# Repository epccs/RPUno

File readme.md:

# RPUno 

From <https://github.com/epccs/RPUno/>

## Overview

A general purpose ATmega328p controller board with level shift IO and current sources that operate over the wide input voltage range.

The bare metal microcontroller on this board is the same as an Arduino Uno, I use it to evaluate the examples. Normally C is my preference so converting Arduino's C++ into C adds some overhead, the toolchain supports both but find fewer surprises with C. The toolchain is available on most Linux distributions, a Raspberry Pi makes a nice remote computer and can handle networking services robustly. I use SSH to log in to the remote Raspberry Pi and then I can pull updates from GitHub and run the "Makefile" rules that compile and upload the firmware. The mezzanine board [RPUadpt] or [RPUpi] can be used to add a multidrop serial (rpubus). This controller can turn off its shield VIN pin to power down the Raspberry Pi on RPUpi.

[RPUadpt]: https://github.com/epccs/RPUadpt
[RPUpi]: https://github.com/epccs/RPUpi

[Forum](https://rpubus.org/bb/viewforum.php?f=6)

[HackaDay](https://hackaday.io/project/12784-rpuno)

## Status

Note: bootloader speed has changed from 115.2k to 38.4k bps due to upload errors with the new transceiver on RPUpi^4. Command line serial speed was changed to 38.4k bps some time ago. I have no clue how the bootload upload was working.

[Options](./Hardware#bill-of-materials)

## [Hardware](./Hardware)

Hardware files and notes for referance.

## Example with RPU BUS

This example shows a multidrop serial bus that has several microcontroller boards connected to a single Raspberry Pi computer. Linux on the single board computer controls a hardware UART (/dev/ttyAMA0) that has serial lines connected to a transceiver and its differential pairs. The remote boards have a [RPUadpt] mezzanine board and CAT5 cable daisy-chain between them. 

[Irrigate7]: https://github.com/epccs/Irrigate7

The transceivers are automatically activated, so common serial programs (e.g. avrdude, PySerial, picocom, and UART libraries) work without modification, but care must be taken to ensure only one controller answeres a host command. Each mezzanine board has a bus manager that is used to disconnect all the serial devices when the host connects, only the bootload target controller is connected. The host tells the manager what target to bootload over I2C (either using the local target controller or directly with 328pb second I2C interface). When the target runs its application and reads the bus address over I2C from the manager the manager broadcast a normal mode state that causes all the managers with valid controllers to connect to the serial lines.

I rely on a Command Line Interface (CLI) to the controllers. The CLI responds to commands terminated with a newline (inspired by console), press enter (which sends a newline) to start a command. The command includes an address with the first two bytes, but echo starts after the second byte is sent. The first byte will cause any transmitting device to stop and dump its outgoing buffer which prevents collisions in the data from the controllers to the host. The command length is also limited to allow the use of optimized buffer size.

As a short example, I'll connect with SSH (e.g. from a Windows 1809 build) to a Raspberry Pi Zero board. These machines have matching usernames, with configured SSH keys and known host file from a previous session. Once on the armv61 machine, I use picocom to interact with two different control boards. They are on the same serial bus at addresses '/1' and '/0' (note that ASCII '1' is 0x31, and ASCII '0' is 0x30, so they have an address that looks good on picocom but is probably not what was expected).

```
C:\Users\rsutherland>ssh pi1.local
Linux pi1 4.14.79+ #1159 Sun Nov 4 17:28:08 GMT 2018 armv6l

The programs included with the Debian GNU/Linux system are free software;
the exact distribution terms for each program are described in the
individual files in /usr/share/doc/*/copyright.

Debian GNU/Linux comes with ABSOLUTELY NO WARRANTY, to the extent
permitted by applicable law.
Last login: Sat Feb 16 12:24:59 2019 from 192.168.4.6
rsutherland@pi1:~ $ picocom -b 38400 /dev/ttyAMA0
picocom v1.7

port is        : /dev/ttyAMA0
flowcontrol    : none
baudrate is    : 38400
parity is      : none
databits are   : 8
escape is      : C-a
local echo is  : no
noinit is      : no
noreset is     : no
nolock is      : no
send_cmd is    : sz -vv
receive_cmd is : rz -vv
imap is        :
omap is        :
emap is        : crcrlf,delbs,

Terminal ready
/0/id?
{"id":{"name":"NightLight","desc":"RPUno (14140^9) Board /w atmega328p","avr-gcc":"5.4.0"}}
/1/id?
{"id":{"name":"AmpHr","desc":"RPUlux (17323^2) Board /w atmega328p","avr-gcc":"5.4.0"}}
Ctrl-a,Ctrl-x 
Thanks for using picocom
rsutherland@pi1:~ $ exit
logout
Connection to pi1.local closed.

C:\Users\rsutherland>
```

At present, I'm using [I2Cdebug] to set the manager bootload address. 

[I2Cdebug]: ./i2c-debug

## AVR toolchain

The core files for this board are in the /lib folder. Each example has its files and a Makefile in its own folder. The toolchain packages that I use are available on Ubuntu and Raspbian. 

```
sudo apt-get install make git gcc-avr binutils-avr gdb-avr avr-libc avrdude
git clone https://github.com/epccs/RPUno
```

packages on ubuntu are from Debain

* [gcc-avr](https://packages.ubuntu.com/search?keywords=gcc-avr)
* [binutils-avr](https://packages.ubuntu.com/search?keywords=binutils-avr)
* [gdb-avr](https://packages.ubuntu.com/search?keywords=gdb-avr)
* [avr-libc](https://packages.ubuntu.com/search?keywords=avr-libc)
* [avrdude](https://packages.ubuntu.com/search?keywords=avrdude)

The repository of binutils-avr for Debian is at

https://salsa.debian.org/debian/binutils-avr

The upstream where it was started from is 

https://www.gnu.org/software/binutils/

I don't see any AVR stuff in the upstream. Atmel must have forked it, and Debian is just patching critical material on the fork. Sadly I get the idea that these build tools are the last thing Microchip wants to mess with, I do not blame them it is a cluster, but it could be improved if they would start a public Github or Gitlab repository for these tools so I could have a place to contribute. Ideally, these updates would be added to the upstream, but I suspect that is not practical. Arduino uses these tools also, but they mainly want responsibility for there IDE. 

I place a [Bootloader] on the bare metal microcontroller with a fuse step and a step that uploads using an ISP tool. 

[Bootloader]: https://github.com/epccs/RPUno/tree/master/Bootloader

```
cd RPUno/Bootloader
# note /dev/ttyACM0 is my ICSP tool.
make fuse
make isp
```

The other applications are loaded through the bootloader using the host serial port. Note that the fuse cannot be changed with the bootloader thus reducing user issues with an application upload.

```
cd ~/RPUno/Adc
# note /dev/ttyUSB0 is my FTDI USBuart, and /dev/ttyAMA0 is my Raspberry Pi
make bootload
```

The software is a guide, it is in C because that is my preference for microcontrollers. If you want additional software please add a Github issue to this repository where we can discuss it. 

## Continuous Integration

Continuous Integration (CI) is the practice of automatically compiling and testing each time the mainline source is updated (e.g. git push). Travis CI is using a version of Ubuntu as there host environment for doing the test build. The build machine allows pulling in any packages I want including the AVR cross compiler. I don't do anything fancy, just run make. A rule like "make test" could be used if the test build machine had hardware connected (e.g. "make bootload" and then "make test") to the machine, but that is not practical in the foreseeable future. This was fairly simple to set up for Travis because the ATmega328p was in production at the time the Ubuntu toolchain was done.

[https://travis-ci.org/epccs/RPUno](https://travis-ci.org/epccs/RPUno)

Update: Travis has Ubuntu [Xenial] 16.04.

[Xenial]: https://docs.travis-ci.com/user/reference/xenial/

## Arduino IDE with Arduino 328p Core

The Arduino [IDE] can use the [Uno's AVR core] files that are included (my [core] files are C rather than C++), just remember to look at the schematic to see how the "Uno" is connected.  I do not use the Arduino IDE or C++ (I am a hardware designer,.and have limited intrest in software).

[IDE]: https://www.arduino.cc/
[Uno's AVR core]: https://github.com/arduino/ArduinoCore-avr
[core]: https://github.com/epccs/RPUno/tree/master/lib

## Visual Studio Code

VSC is one of the editors I use, and it is happy with Makefiles. The feature I like most is [IntelliSense], which is configured with JSON files in [.vscode]. 

[IntelliSense]: https://code.visualstudio.com/docs/editor/intellisense
[.vscode]: https://github.com/epccs/RPUno/tree/master/.vscode

The best way to use VSC with GCC (avr-gcc) is in an environment that just works, for me that is Linux, so I can enable [WSL] and install Ubuntu and then use the [Remote WSL].

[WSL]: https://docs.microsoft.com/en-us/windows/wsl/install-win10
[Remote WSL]: https://code.visualstudio.com/docs/remote/wsl

or I can install Linux on a 64bit x86 machine and use [Remote SSH].

[Remote SSH]: https://code.visualstudio.com/docs/remote/ssh

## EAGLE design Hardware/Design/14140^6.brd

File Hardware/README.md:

# Hardware

## Overview

ATmega328p based controller board with options for DIN mounts and 3.5mm spaced through-hole for user connections and headers. Eight level shifted (same as VIN range) digital I/O (10, 11, 12, 13, 14*, 15*, 16*, 17*), the last four (*) are analog channels (0, 1, 2, 3). Four 22mA current source used with loop sensors are available with enables (5, 6, 3, 4). One 17mA current source for a pulse sensor and it has an enable (7). ICP1 is pulled down when enough current (>7mA) arrives from the pulse sensor. Alternate power input may be enabled (9), and power to the shield VIN pin may be disabled (2). Power with 7 thru 36V DC.

The ATmega328p can be programmed with the GCC based toolchain for AVR found in Debian packages (it is available on, Ubuntu, Raspbian, Mac via brew, Windows via Windows Subsystem for Linux). Bootloader options include [optiboot] and [xboot]. Serial bootloaders cannot change the hardware fuse setting which reduces the occurrence of accidentally bricking the controller (I recommend using a serial bootloader during application development). Note that [optiboot] clears the watchdog so it will not get stuck in a watchdog loop.

[optiboot]: https://github.com/Optiboot/optiboot
[xboot]: https://github.com/alexforencich/xboot

## Inputs/Outputs/Functions

```
        Toolchain: gcc-avr binutils-avr gdb-avr avr-libc avrdude
        Wide input power range from 7..36V DC
        High side current sense on input power connected to ADC6.
        Input power voltage is divided down and connected to ADC7.
        Eight digital input/outputs (10,11,12,13,14*,15*,16*,17*) with level conversion.
        Four of the DIO may be used for ADC (*) channels 0..3 (ADC0,ADC1,ADC2,ADC3)
        Four 22mA current sources with enable (3,4,5,6).
        One 17mA current source with enable (7).
        Power to the shield VIN pin may be disabled (2).
        Alternate power input may be enabled (9).
        MCU power (+5V) is converted with an SMPS from the 7..36V input power.
```

## Uses

```
        General Purpose Control for Automation
            Bare Matal (e.g. infinite main loop checks inputs, performs algorithm, and writes outputs)
        Data Acquisition using Capture Hardware (ICP1).
            Flow Meter
            Rotating Hardware
            Pulse Output Temperature Sensors
            Pulse Output Capacitance Sensors
        Automation
            Shield VIN pin can power down a Raspberry Pi on the RPUpi shield.
            A current source may string through inputs of multiple Solid State Relays to control multi-phase power.
            Program in C with an open source toolchain (e.g. GCC, avrdude...).
```

## Notice

```
        ADC4 and ADC5 are used for I2C exclusively and not routed to the analog header.
        AREF from ATmega328p is not routed to the header.
        3V3 is not present on the board, the header pin is not connected.
```

# Table Of Contents

1. [Status](#status)
2. [Design](#design)
3. [Bill of Materials](#bill-of-materials)
4. [Assembly](#assembly)
5. [How To Use](#how-to-use)

# Status

```
        ^9  Done: Design, Layout, BOM, Review*, Order Boards, Assembly, Testing,
            WIP: Evaluation.
            Todo: 
            *during review the Design may change without changing the revision.
            Remove ICP1 10mA pull-up
            Replace digital curr sources with CS2 and CS3
            Replace IO3 and IO4 with ADC2 and ADC3
            Swap MOSI (IO11) with ADC3
            Use IO3 and IO4 to enalbe 22mA CS2 and CS3
            Add level shift to ADC0 and ADC1 so they can be used as digital IO
            Add bootload port (e.g. for Adafruit Friend)
            Add alternate power input (e.g. disconnect a solar pannel to stop charge)
            Pull-down IO9 and 100k ohm on zener to make sure alt power is off at init

        ^8  Done: Design, Layout, BOM, Review*, Order Boards,
            all boards scraped, no assembly done

        ^7  Done: Design, Layout, BOM, Review*, Order Boards, Assembly, Testing,
            WIP: Evaluation.
            use an ESD_NODE like Irrigate7.
            don't turn off the current source used with digital outputs since the digital IO's can do that. 
            DIO protection resistor (change 182 Ohm to 127 Ohm)
            remove LT3652 and reduce size of board.
            add an IDC connector for everything that was used with LT3652 (5,6,7,ADC2,ADC3).
            add JSK plug for I2C
            location: 2017-11-1 reflow oven.

        ^6  two test units (T1,T2) made, four units made to see if anyone is intrested.
            location: 2017-3-24 T1^6 damaged MCU while taking power example image.
                    2017-3-25 T2^6 using on test bench.
                    2017-6-12 T1^6 replaced MCU from a scrped RPUno^4 and tested again.
                    2017-7-19 T2^6 + RPUadpt^5 in SEncl NightLight testing.
                    2017-8-26 T2^6 NightLight ended, unit is in an enclosure with battey but is not in use.
                    2018-4-15 T1 and T2 scap.

        ^5  only unit of this version made
            location: 2016-12-18 Test Bench /w an RPUpi^1, start power management testing
                    2017-1-1 had ADC7 parts (and BOM) changed to measre battery.
                    2017-1-5 had ADC6 hacked to measure raw PV.
                    2017-2-4 moved to SWall Encl /w K3^1, RPUadpt^4, SLP003-12U, 12V battery.
                    2017-3-19 remove 10k thermistor which was used by  LT3652 to turn off chrg when over 40 C
                    2017-4-17 running Solenoid fw, @ SWall Encl, Update K3^2, Update RPUadpt^5, SLP003-12U, 12V battery.
```

Debugging and fixing problems i.e. [Schooling](./Schooling/)

Setup and methods used for [Evaluation](./Evaluation/)

# Design

The board is 0.063 thick, FR4, two layer, 1 oz copper with ENIG (gold) finish.

## Electrical Parameters

```
Power Voltage: 7 thru 36V
```

## Mounting

```
        DIN rail
```

## Electrical Schematic

## Testing

Check correct assembly and function with [Testing](./Testing/)

# Bill of Materials

The BOM is a CVS file, import it into a spreadsheet program like LibreOffice Calc (or Excel), or use a text editor.

Option | BOM's included
----- | ----- 
A. | [BRD] 
M. | [BRD] [SMD] [HDR] 
W. | [BRD] [SMD] [HDR] [PLUG]
Z. | [BRD] [SMD] [HDR] [PLUG] [DIN]

[BRD]: ./Design/14140BRD,BOM.csv
[SMD]: ./Design/14140SMD,BOM.csv
[HDR]: ./Design/14140HDR,BOM.csv
[PLUG]: ./Design/14140PLUG,BOM.csv
[DIN]: ./Design/14140DIN,BOM.csv

[Order Form](https://rpubus.org/Order_Form.html)

# Assembly

## SMD

The board is assembled with CHIPQUIK no-clean solder SMD291AX (RoHS non-compliant). 

The SMD reflow is done in a Black & Decker Model NO. TO1303SB which has the heating elements controlled by a Solid State Relay and an ATMega328p loaded with this [Reflow] firmware.

[Reflow]: https://github.com/epccs/RPUno/tree/master/Reflow

# How To Use

The application should have a wiring diagram to show the setup.

## Solar

Trickle charging a battery can be done directly through a diode when the PV source is less than or about .02C (e.g. 200mA into a 10AHr battery). This means that the need for a charge controller depends on if the user wants to size the PV and battery storage for trickle or quick charging (i.e. >0.02C). When I use an SLP003-12U panel that charges at less than 200mA and a 10AHr AGM battery with a diode that blocks dark current no charge controller is needed. 

## Input Power LC 

Input wiring can have inductance that oscilates as an [LC circuit] with the input capacitor. The problem can show up when the SMPS has a frequancy component that drives the oscilation. There are many ways to deal with the issue, a few examples include twisting the input power wires to lower there inductance, adding a ferite to dampen the oscilation, adding a bypass or two along the line to shift the oscilation nodes.

[LC circuit]: https://en.wikipedia.org/wiki/LC_circuit

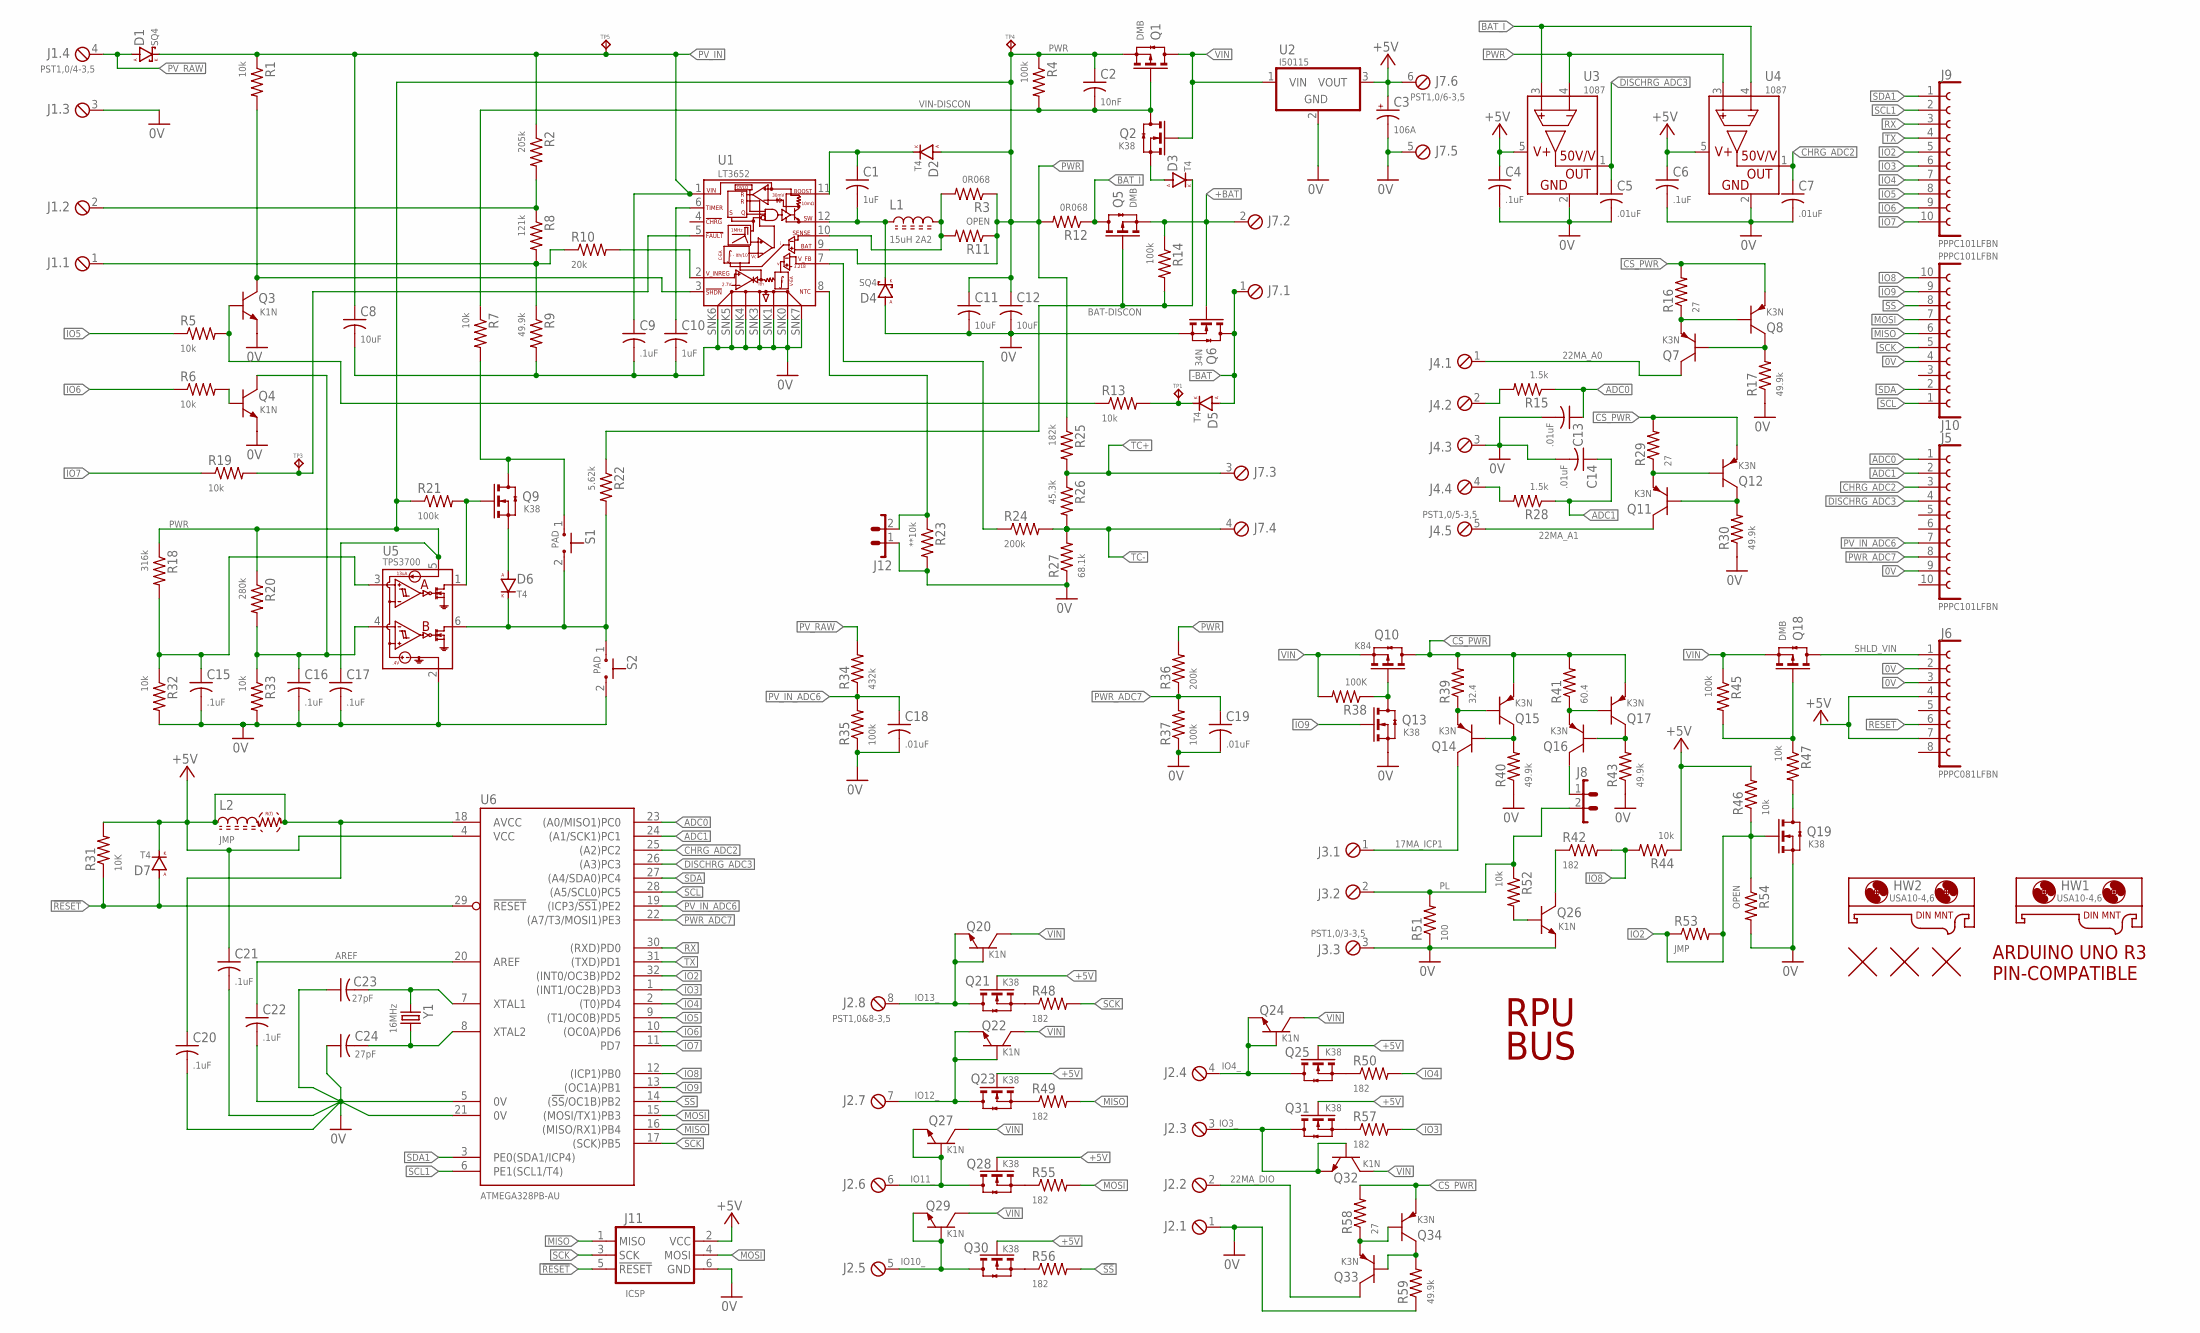
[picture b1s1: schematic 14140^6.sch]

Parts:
C1, C10: 1uF; C0805(2012)
C2: 10nF; C0603(1608)
C3: 106A; 3216
C4, C6, C15, C16, C17, C20, C21, C22: .1uF; C0603(1608)
C5, C7, C13, C14, C18, C19: .01uF; C0603(1608)
C8, C11, C12: 10uF; C1206(3216)
C9: .1uF; C0805(2012)
C23, C24: 27pF; C0603(1608)
D1, D4: SQ4; SMA
D2, D3, D5, D6, D7: T4; SOD123
HW1, HW2: USA10-4,6; USA10
J1: PST1,0/4-3,5; MCV4
J2: PST1,0&8-3,5; MCV8
J3: PST1,0/3-3,5; MCV3
J4: PST1,0/5-3,5; MCV5
J5, J9, J10: PPPC101LFBN; F1X10
J6: PPPC081LFBN; F1X8
J7: PST1,0/6-3,5; MCV6
J8, J12: 1X2
J11: ICSP; ISP
L1: 15uH 2A2; L3939
L2: JMP; C0805(2012)
Q1, Q5, Q18: DMB; SOT23
Q2, Q9, Q13, Q19, Q21, Q23, Q25, Q28, Q30, Q31: K38; SOT23
Q3, Q4, Q20, Q22, Q24, Q26, Q27, Q29, Q32: K1N; SOT23
Q6: 34N; SOT23
Q7, Q8, Q11, Q12, Q14, Q15, Q16, Q17, Q33, Q34: K3N; SOT23
Q10: K84; SOT23
R1, R5, R6, R7, R13, R19, R32, R33, R44, R46, R47, R52: 10k; C0805(2012)
R2: 205k; C0805(2012)
R3, R12: 0R068; C1210(3225)
R4, R14, R21, R35, R37, R45: 100k; C0805(2012)
R8: 121k; C0805(2012)
R9, R17, R30, R40, R43, R59: 49.9k; C0805(2012)
R10: 20k; C0805(2012)
R11: OPEN; C1210(3225)
R15, R28: 1.5k; C0805(2012)
R16, R29, R58: 27; C0805(2012)
R18: 316k; C0805(2012)
R20: 280k; C0805(2012)
R22: 5.62k; C0805(2012)
R23: **10k; C0805(2012)
R24, R36: 200k; C0805(2012)
R25: 182k; C0805(2012)
R26: 45.3k; C0805(2012)
R27: 68.1k; C0805(2012)
R31: 10K; C0805(2012)
R34: 432k; C0805(2012)
R38: 100K; C0805(2012)
R39: 32.4; C0805(2012)
R41: 60.4; C0805(2012)
R42, R48, R49, R50, R55, R56, R57: 182; C0805(2012)
R51: 100; C0805(2012)
R53: JMP; C0805(2012)
R54: OPEN; C0805(2012)
S1, S2: PAD; C0805(2012)
TP1, TP3, TP4, TP5: TPPAD1-08; P1-08
U1: LT3652; 12MSOP-EDP-HAND
U2: I50115; OKI-78SR-H
U3, U4: 1087; SOT23-5
U5: TPS3700; SOT23-6
U6: ATMEGA328PB-AU; TQFP32-08
U$1: ARDUINO-UNO; ARDUINO_UNO
U$2, U$3, U$4: FIDUCIAL1.27; FIDUCIAL-1.27
Y1: 16MHz; CSM-3X

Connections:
0V: C3.-, C4.2, C5.2, C6.2, C7.2, C8.2, C9.2, C10.2, C11.2, C12.2, C13.2, C14.2, C15.2, C16.2, C17.2, C18.2, C19.2, C20.2, C21.2, C22.2, C23.1, C24.1, D4.A, J1.3, J2.1, J3.3, J4.3, J5.9, J6.2, J6.3, J7.5, J10.4, J11.6 (GND), J12.1, Q3.E, Q4.E, Q6.2(S) (S), Q13.2(S) (S), Q19.2(S) (S), Q26.E, R9.2, R17.1, R23.2, R27.1, R30.1, R32.2, R33.2, R35.1, R37.1, R40.1, R43.1, R51.1, R54.2, R59.1, S2.2 (3), U1.SNK0 (0V), U1.SNK1 (0V), U1.SNK3 (0V), U1.SNK4 (0V), U1.SNK5 (0V), U1.SNK6 (0V), U1.SNK7 (0V), U2.2 (GND), U3.2 (GND), U4.2 (GND), U5.2 (0V), U6.5 (0V), U6.21 (0V)
17MA_ICP1: J3.1, Q14.C
22MA_A0: J4.1, Q7.C
22MA_A1: J4.5, Q11.C
22MA_DIO: J2.2, Q33.C
!FAULT: R19.2, TP3.TP, U1.5 (!FAULT)
!RESET!: D7.A, J6.6, J11.5 (!RESET), R31.1, U6.29 (!RESET)
!SS: J10.8, R56.2, U6.14 ((!SS!/OC1B)PB2)
+5V: C3.+, C4.1, C6.1, C20.1, C21.1, D7.C (K), J6.4, J6.7, J7.6, J11.2 (VCC), L2.1, L2.2, Q21.1(G) (G), Q23.1(G) (G), Q25.1(G) (G), Q28.1(G) (G), Q30.1(G) (G), Q31.1(G) (G), R31.2, R44.1, R46.2, U2.3 (VOUT), U3.5 (VCC), U4.5 (VCC), U6.4 (VCC), U6.18 (AVCC)
+BAT: J7.2, Q5.2(S) (S), Q6.1(G) (G), R14.1
-BAT: D5.A, J7.1, Q6.3(D) (D)
ADC0: C13.1, J5.1, R15.1, U6.23 ((A0/MISO1)PC0)
ADC1: C14.1, J5.2, R28.1, U6.24 ((A1/SCK1)PC1)
AREF: C22.1, U6.20 (AREF)
BAT-DISCON: D3.C (K), Q5.1(G) (G), R14.2, R22.1
BAT_I: Q5.3(D) (D), R12.1, U3.3 (S+), U4.4 (S-)
CHRG_ADC2: C7.1, J5.3, U4.1 (OUT), U6.25 ((A2)PC2)
CS_PWR: Q8.E, Q10.3(D) (D), Q12.E, Q15.E, Q17.E, Q34.E, R16.2, R29.2, R39.2, R41.2, R58.2
DISCHRG_ADC3: C5.1, J5.4, U3.1 (OUT), U6.26 ((A3)PC3)
IO2: J9.5, Q19.1(G) (G), R46.1, R53.1, R53.2, R54.1, U6.32 ((INT0/OC3B)PD2)
IO3: J9.6, R57.2, U6.1 ((INT1/OC2B)PD3)
IO3_: J2.3, Q31.3(D) (D), Q32.B, Q32.E
IO4: J9.7, R50.2, U6.2 ((T0)PD4)
IO4_: J2.4, Q24.B, Q24.E, Q25.3(D) (D)
IO5: J9.8, R5.1, U6.9 ((T1/OC0B)PD5)
IO6: J9.9, R6.1, U6.10 ((OC0A)PD6)
IO7: J9.10, R19.1, U6.11 (PD7)
IO8: J10.10, R42.2, R44.2, U6.12 ((ICP1)PB0)
IO9: J10.9, Q13.1(G) (G), U6.13 ((OC1A)PB1)
IO10_: J2.5, Q29.B, Q29.E, Q30.3(D) (D)
IO11_: J2.6, Q27.B, Q27.E, Q28.3(D) (D)
IO12_: J2.7, Q22.B, Q22.E, Q23.3(D) (D)
IO13_: J2.8, Q20.B, Q20.E, Q21.3(D) (D)
MISO: J10.6, J11.1 (MISO), R49.2, U6.16 ((MISO/RX1)PB4)
MOSI: J10.7, J11.4 (MOSI), R55.2, U6.15 ((MOSI/TX1)PB3)
unnamed: C10.1, U1.6 (TIMER)
unnamed: R24.1, U1.7 (V_FB)
unnamed: J1.1, R8.2, R9.1, R10.1
unnamed: Q3.C, R1.2, U1.3 (!SHDN)
unnamed: Q4.B, R6.2
unnamed: C16.1, Q4.C, R20.2, R33.1, U5.4 (INB)
unnamed: D3.A, Q2.2(S) (S)
unnamed: J1.2, R2.2, R8.1
unnamed: C1.1, D2.C (K), U1.11 (BOOST)
unnamed: R10.2, U1.2 (V_INREG)
unnamed: D5.C (K), R13.2, TP1.TP
unnamed: D6.A, Q9.2(S) (S)
unnamed: C15.1, R18.2, R32.1, U5.3 (INA)
unnamed: Q9.1(G) (G), R21.2, U5.1 (OUTA)
unnamed: D6.C (K), R22.2, S1.2 (3), S2.1, U5.6 (OUTB)
unnamed: Q9.3(D) (D), R7.2, S1.1
unnamed: J8.1, Q16.C
unnamed: Q7.E, Q8.B, R16.1
unnamed: Q23.2(S) (S), R49.1
unnamed: Q28.2(S) (S), R55.1
unnamed: Q7.B, Q8.C, R17.2
unnamed: J4.2, R15.2
unnamed: Q10.1(G) (G), Q13.3(D) (D), R38.1
unnamed: Q30.2(S) (S), R56.1
unnamed: J4.4, R28.2
unnamed: Q11.E, Q12.B, R29.1
unnamed: Q11.B, Q12.C, R30.2
unnamed: Q33.E, Q34.B, R58.1
unnamed: Q31.2(S) (S), R57.1
unnamed: Q25.2(S) (S), R50.1
unnamed: Q33.B, Q34.C, R59.2
unnamed: Q21.2(S) (S), R48.1
unnamed: Q18.1(G) (G), R45.2, R47.1
unnamed: Q19.3(D) (D), R47.2
unnamed: Q3.B, R5.2, R13.1
unnamed: Q26.B, R52.2
unnamed: Q26.C, R42.1
unnamed: Q14.E, Q15.B, R39.1
unnamed: C23.2, U6.7 (XTAL1), Y1.1
unnamed: C24.2, U6.8 (XTAL2), Y1.2
unnamed: Q14.B, Q15.C, R40.2
unnamed: Q16.E, Q17.B, R41.1
unnamed: Q16.B, Q17.C, R43.2
NTC1: J12.2, R23.1, U1.8 (NTC)
PL: J3.2, J8.2, R51.2, R52.1
PV_IN: C8.1, C9.1, D1.K, R1.1, R2.1, TP5.TP, U1.1 (VIN)
PV_IN_ADC6: C18.1, J5.7, R34.1, R35.2, U6.19 ((ICP3/!SS1!)PE2)
PV_RAW: D1.A, J1.4, R34.2
PWR: C2.1, C11.1, C12.1, C17.1, D2.A, Q1.2(S) (S), R3.1, R4.1, R11.1, R12.2, R18.1, R20.1, R21.1, R25.1, R36.2, TP4.TP, U1.9 (BAT), U3.4 (S-), U4.3 (S+), U5.5 (VDD)
PWR_ADC7: C19.1, J5.8, R36.1, R37.2, U6.22 ((A7/T3/MOSI1)PE3)
RX: J9.3, U6.30 ((RXD)PD0)
SCK: J10.5, J11.3 (SCK), R48.2, U6.17 ((SCK)PB5)
SCL: J10.1, U6.28 ((A5/SCL0)PC5)
SCL1: J9.2, U6.6 (PE1(SCL1/T4))
SDA: J10.2, U6.27 ((A4/SDA0)PC4)
SDA1: J9.1, U6.3 (PE0(SDA1/ICP4))
SENSE: L1.2, R3.2, R11.2, U1.10 (SENSE)
SHLD_VIN: J6.1, Q18.3(D) (D)
SW: C1.2, D4.K, L1.1, U1.12 (SW)
TC+: J7.3, R25.2, R26.1
TC-: J7.4, R24.2, R26.2, R27.2
TX: J9.4, U6.31 ((TXD)PD1)
VIN: Q1.3(D) (D), Q2.1(G) (G), Q10.2(S) (S), Q18.2(S) (S), Q20.C, Q22.C, Q24.C, Q27.C, Q29.C, Q32.C, R38.2, R45.1, U2.1 (VIN)
VIN-DISCON: C2.2, Q1.1(G) (G), Q2.3(D) (D), R4.2, R7.1

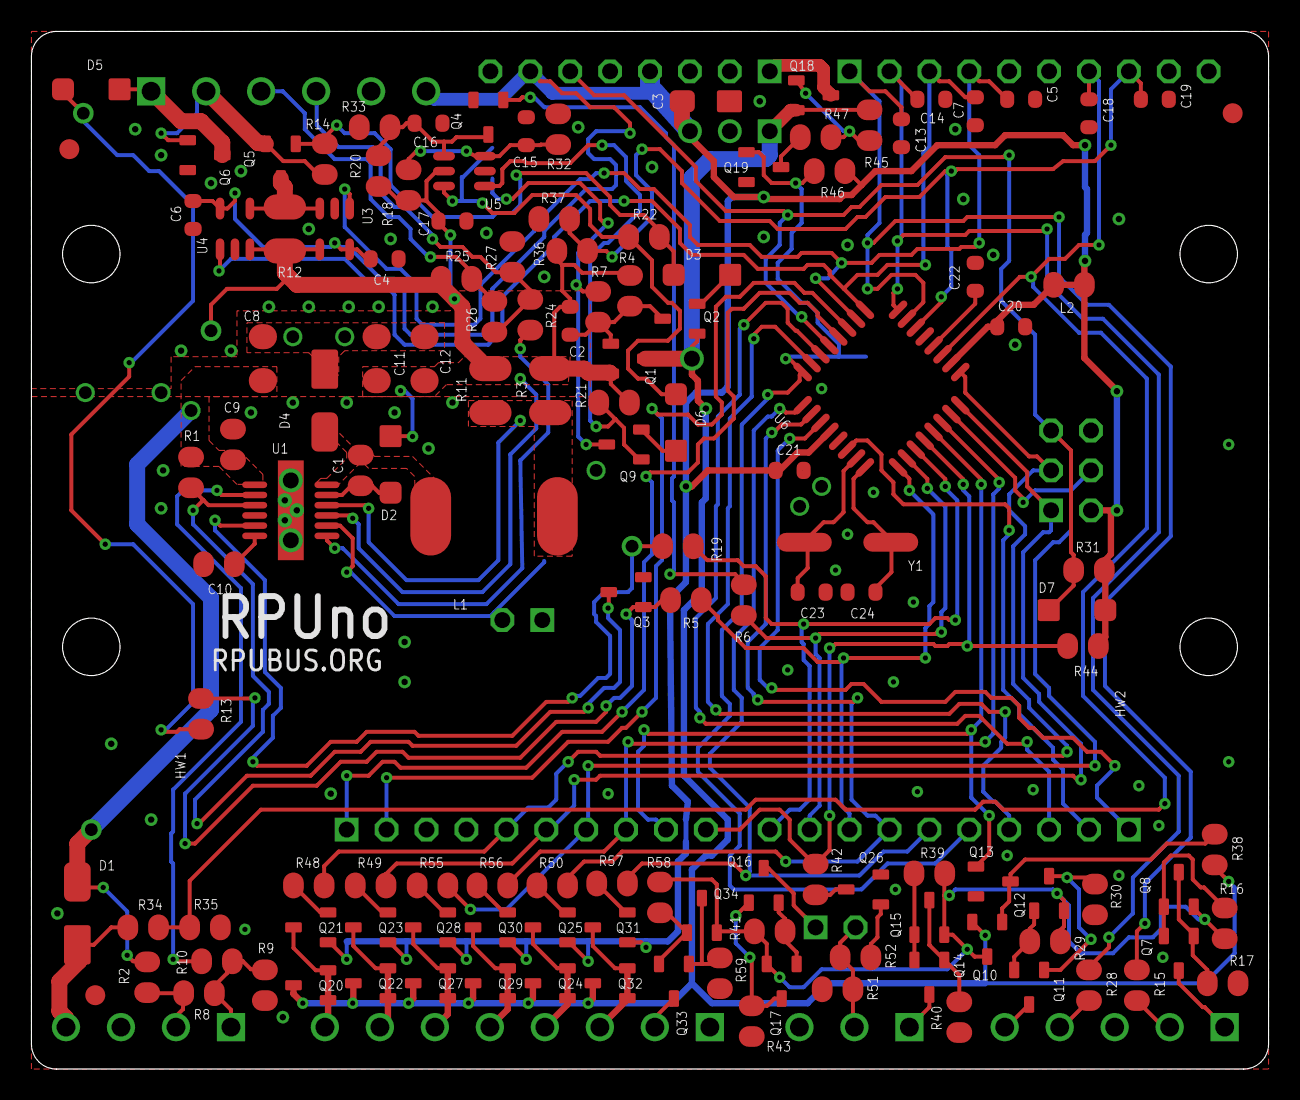
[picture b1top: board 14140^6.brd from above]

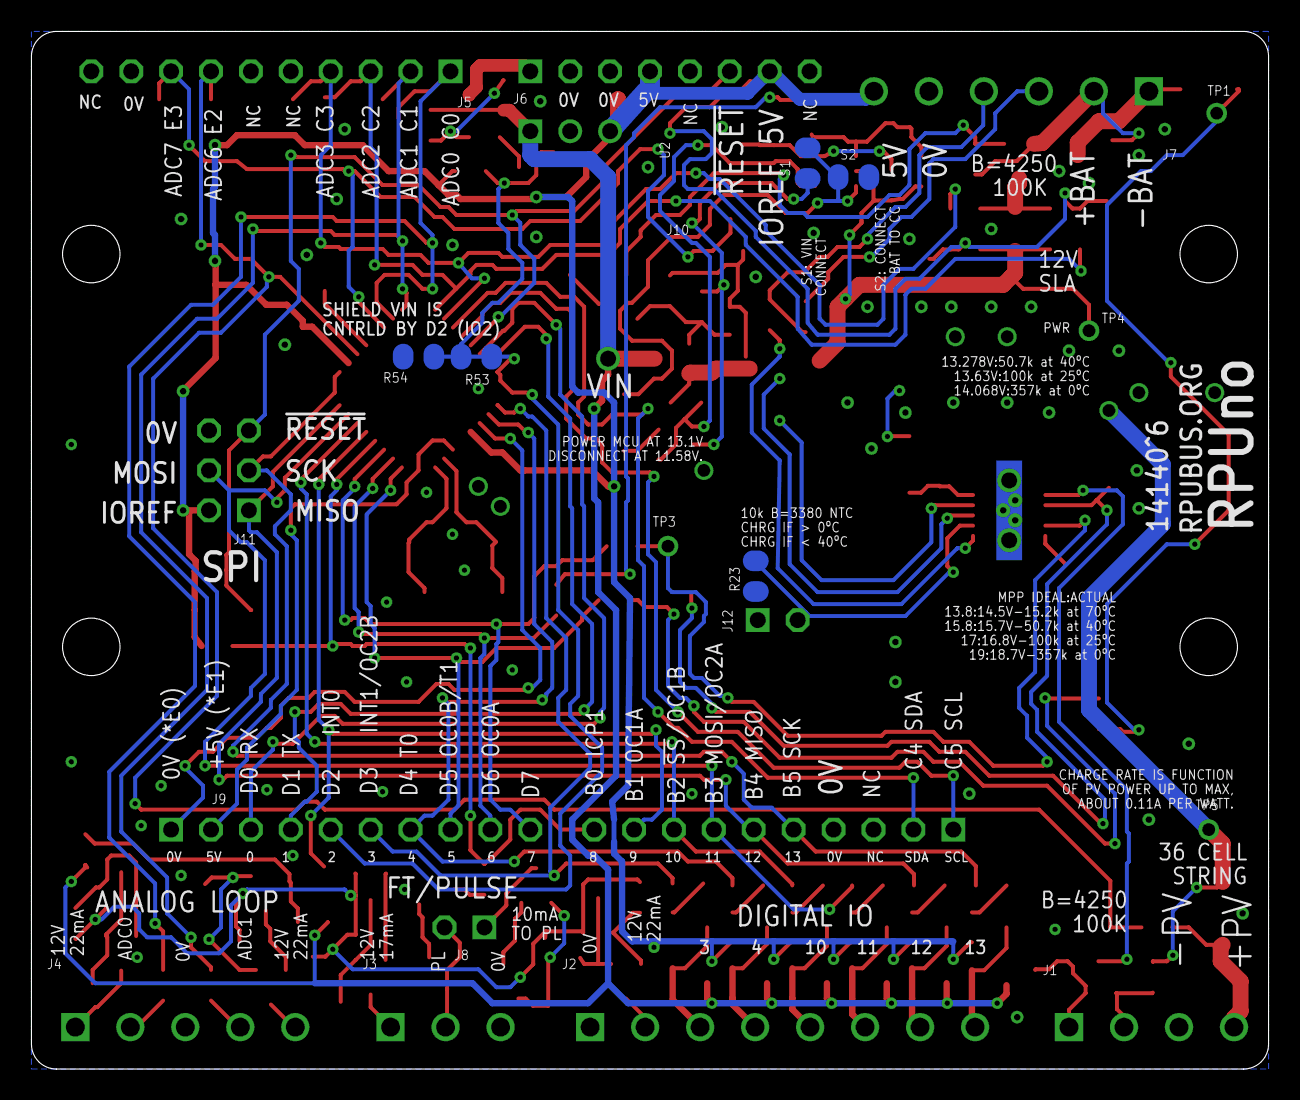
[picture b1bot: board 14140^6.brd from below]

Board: 2 copper layers, 78.7 x 66.0 mm, 157 parts (23 on the bottom side), 99 nets.

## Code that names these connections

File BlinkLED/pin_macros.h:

/*
io macros for AVR chips 
*/

//input 
#define a0_input DDRA &= ~_BV(PA0)
#define a1_input DDRA &= ~_BV(PA1)
#define a2_input DDRA &= ~_BV(PA2)
#define a3_input DDRA &= ~_BV(PA3)
#define a4_input DDRA &= ~_BV(PA4)
#define a5_input DDRA &= ~_BV(PA5)
#define a6_input DDRA &= ~_BV(PA6)
#define a7_input DDRA &= ~_BV(PA7)

#define b0_input DDRB &= ~_BV(PB0)
#define b1_input DDRB &= ~_BV(PB1)
#define b2_input DDRB &= ~_BV(PB2)
#define b3_input DDRB &= ~_BV(PB3)
#define b4_input DDRB &= ~_BV(PB4)
#define b5_input DDRB &= ~_BV(PB5)
#define b6_input DDRB &= ~_BV(PB6)
#define b7_input DDRB &= ~_BV(PB7)

#define c0_input DDRC &= ~_BV(PC0)
#define c1_input DDRC &= ~_BV(PC1)
#define c2_input DDRC &= ~_BV(PC2)
#define c3_input DDRC &= ~_BV(PC3)
#define c4_input DDRC &= ~_BV(PC4)
#define c5_input DDRC &= ~_BV(PC5)
#define c6_input DDRC &= ~_BV(PC6)
#define c7_input DDRC &= ~_BV(PC7)

#define d0_input DDRD &= ~_BV(PD0)
#define d1_input DDRD &= ~_BV(PD1)
#define d2_input DDRD &= ~_BV(PD2)
#define d3_input DDRD &= ~_BV(PD3)
#define d4_input DDRD &= ~_BV(PD4)
#define d5_input DDRD &= ~_BV(PD5)
#define d6_input DDRD &= ~_BV(PD6)
#define d7_input DDRD &= ~_BV(PD7)

#define e0_input DDRE &= ~_BV(PE0)
#define e1_input DDRE &= ~_BV(PE1)
#define e2_input DDRE &= ~_BV(PE2)
#define e3_input DDRE &= ~_BV(PE3)
#define e4_input DDRE &= ~_BV(PE4)
#define e5_input DDRE &= ~_BV(PE5)
#define e6_input DDRE &= ~_BV(PE6)
#define e7_input DDRE &= ~_BV(PE7)

//output
#define a0_output DDRA|= _BV(PA0)
#define a1_output DDRA|= _BV(PA1)
#define a2_output DDRA|= _BV(PA2)
#define a3_output DDRA|= _BV(PA3)
#define a4_output DDRA|= _BV(PA4)
#define a5_output DDRA|= _BV(PA5)
#define a6_output DDRA|= _BV(PA6)
#define a7_output DDRA|= _BV(PA7)

#define b0_output DDRB|= _BV(PB0)
#define b1_output DDRB|= _BV(PB1)
#define b2_output DDRB|= _BV(PB2)
#define b3_output DDRB|= _BV(PB3)
#define b4_output DDRB|= _BV(PB4)
#define b5_output DDRB|= _BV(PB5)
#define b6_output DDRB|= _BV(PB6)
#define b7_output DDRB|= _BV(PB7)

#define c0_output DDRC|= _BV(PC0)
#define c1_output DDRC|= _BV(PC1)
#define c2_output DDRC|= _BV(PC2)
#define c3_output DDRC|= _BV(PC3)
#define c4_output DDRC|= _BV(PC4)
#define c5_output DDRC|= _BV(PC5)
#define c6_output DDRC|= _BV(PC6)
#define c7_output DDRC|= _BV(PC7)

#define d0_output DDRD|= _BV(PD0)
#define d1_output DDRD|= _BV(PD1)
#define d2_output DDRD|= _BV(PD2)
#define d3_output DDRD|= _BV(PD3)
#define d4_output DDRD|= _BV(PD4)
#define d5_output DDRD|= _BV(PD5)
#define d6_output DDRD|= _BV(PD6)
#define d7_output DDRD|= _BV(PD7)

#define e0_output DDRE|= _BV(PE0)
#define e1_output DDRE|= _BV(PE1)
#define e2_output DDRE|= _BV(PE2)
#define e3_output DDRE|= _BV(PE3)
#define e4_output DDRE|= _BV(PE4)
#define e5_output DDRE|= _BV(PE5)
#define e6_output DDRE|= _BV(PE6)
#define e7_output DDRE|= _BV(PE7)

//high
#define a0_high PORTA|= _BV(PA0)
#define a1_high PORTA|= _BV(PA1)
#define a2_high PORTA|= _BV(PA2)
#define a3_high PORTA|= _BV(PA3)
#define a4_high PORTA|= _BV(PA4)
#define a5_high PORTA|= _BV(PA5)
#define a6_high PORTA|= _BV(PA6)
#define a7_high PORTA|= _BV(PA7)

#define b0_high PORTB|= _BV(PB0)
#define b1_high PORTB|= _BV(PB1)
#define b2_high PORTB|= _BV(PB2)
#define b3_high PORTB|= _BV(PB3)
#define b4_high PORTB|= _BV(PB4)
#define b5_high PORTB|= _BV(PB5)
#define b6_high PORTB|= _BV(PB6)
#define b7_high PORTB|= _BV(PB7)

#define c0_high PORTC|= _BV(PC0)
#define c1_high PORTC|= _BV(PC1)
#define c2_high PORTC|= _BV(PC2)
#define c3_high PORTC|= _BV(PC3)
#define c4_high PORTC|= _BV(PC4)
#define c5_high PORTC|= _BV(PC5)
#define c6_high PORTC|= _BV(PC6)
#define c7_high PORTC|= _BV(PC7)

#define d0_high PORTD|= _BV(PD0)
#define d1_high PORTD|= _BV(PD1)
#define d2_high PORTD|= _BV(PD2)
#define d3_high PORTD|= _BV(PD3)
#define d4_high PORTD|= _BV(PD4)
#define d5_high PORTD|= _BV(PD5)
#define d6_high PORTD|= _BV(PD6)
#define d7_high PORTD|= _BV(PD7)

#define e0_high PORTE|= _BV(PE0)
#define e1_high PORTE|= _BV(PE1)
#define e2_high PORTE|= _BV(PE2)
#define e3_high PORTE|= _BV(PE3)
#define e4_high PORTE|= _BV(PE4)
#define e5_high PORTE|= _BV(PE5)
#define e6_high PORTE|= _BV(PE6)
#define e7_high PORTE|= _BV(PE7)

//low
#define a0_low PORTA &= ~_BV(PA0)
#define a1_low PORTA &= ~_BV(PA1)
#define a2_low PORTA &= ~_BV(PA2)
#define a3_low PORTA &= ~_BV(PA3)
#define a4_low PORTA &= ~_BV(PA4)
#define a5_low PORTA &= ~_BV(PA5)
#define a6_low PORTA &= ~_BV(PA6)
#define a7_low PORTA &= ~_BV(PA7)

#define b0_low PORTB &= ~_BV(PB0)
#define b1_low PORTB &= ~_BV(PB1)
#define b2_low PORTB &= ~_BV(PB2)
#define b3_low PORTB &= ~_BV(PB3)
#define b4_low PORTB &= ~_BV(PB4)
#define b5_low PORTB &= ~_BV(PB5)
#define b6_low PORTB &= ~_BV(PB6)
#define b7_low PORTB &= ~_BV(PB7)

#define c0_low PORTC &= ~_BV(PC0)
#define c1_low PORTC &= ~_BV(PC1)
#define c2_low PORTC &= ~_BV(PC2)
#define c3_low PORTC &= ~_BV(PC3)
#define c4_low PORTC &= ~_BV(PC4)
#define c5_low PORTC &= ~_BV(PC5)
#define c6_low PORTC &= ~_BV(PC6)
#define c7_low PORTC &= ~_BV(PC7)

#define d0_low PORTD &= ~_BV(PD0)
#define d1_low PORTD &= ~_BV(PD1)
#define d2_low PORTD &= ~_BV(PD2)
#define d3_low PORTD &= ~_BV(PD3)
#define d4_low PORTD &= ~_BV(PD4)
#define d5_low PORTD &= ~_BV(PD5)
#define d6_low PORTD &= ~_BV(PD6)
#define d7_low PORTD &= ~_BV(PD7)

#define e0_low PORTE &= ~_BV(PE0)
#define e1_low PORTE &= ~_BV(PE1)
#define e2_low PORTE &= ~_BV(PE2)
#define e3_low PORTE &= ~_BV(PE3)
#define e4_low PORTE &= ~_BV(PE4)
#define e5_low PORTE &= ~_BV(PE5)
#define e6_low PORTE &= ~_BV(PE6)
#define e7_low PORTE &= ~_BV(PE7)

//read
#define a0_read PINA & _BV(PA0)
#define a1_read PINA & _BV(PA1)
#define a2_read PINA & _BV(PA2)
#define a3_read PINA & _BV(PA3)
#define a4_read PINA & _BV(PA4)
#define a5_read PINA & _BV(PA5)
#define a6_read PINA & _BV(PA6)
#define a7_read PINA & _BV(PA7)

#define b0_read PINB & _BV(PB0)
#define b1_read PINB & _BV(PB1)
#define b2_read PINB & _BV(PB2)
#define b3_read PINB & _BV(PB3)
#define b4_read PINB & _BV(PB4)
#define b5_read PINB & _BV(PB5)
#define b6_read PINB & _BV(PB6)
#define b7_read PINB & _BV(PB7)

#define c0_read PINC & _BV(PC0)
#define c1_read PINC & _BV(PC1)
#define c2_read PINC & _BV(PC2)
#define c3_read PINC & _BV(PC3)
#define c4_read PINC & _BV(PC4)
#define c5_read PINC & _BV(PC5)
#define c6_read PINC & _BV(PC6)
#define c7_read PINC & _BV(PC7)

#define d0_read PIND & _BV(PD0)
#define d1_read PIND & _BV(PD1)
#define d2_read PIND & _BV(PD2)
#define d3_read PIND & _BV(PD3)
#define d4_read PIND & _BV(PD4)
#define d5_read PIND & _BV(PD5)
#define d6_read PIND & _BV(PD6)
#define d7_read PIND & _BV(PD7)

#define e0_read PINE & _BV(PE0)
#define e1_read PINE & _BV(PE1)
#define e2_read PINE & _BV(PE2)
#define e3_read PINE & _BV(PE3)
#define e4_read PINE & _BV(PE4)
#define e5_read PINE & _BV(PE5)
#define e6_read PINE & _BV(PE6)
#define e7_read PINE & _BV(PE7)

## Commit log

2016-01-24 :circus_tent: Added .gitattributes
2016-01-24 init
    stuff for atmega328p
2016-04-13 April updates
    looking at make files
2016-04-22 Uart is interrupt-driven with stdio redirect
2016-04-26 add parsing
2016-04-27 fix parsing logic and debug msgs
2016-05-11 Capture has been overhaul, it now uses a Makefile
2016-05-11 unused files
2016-05-12 Capture: more updates
2016-05-12 capture? cmd arg[0] now needs to be icp1, and arg[1] is a num from 1..15
2016-05-20 Analog auto conversion
    Testing Solar and Battery voltage reading
2016-05-21 Capture: fix JSON so it is easy to convert into cvs
    also add loop with delay
2016-05-21 Capture: use of word count was confusing in readme
2016-05-26 many updates
    add Eeprom, use id.c in Uart for other applications, this shows how
    Makefiles can be used to develop and test the modular parts of a
    interactive command interface.
2016-05-30 analog and capture updates
    adc auto trigger reads channels and then needs started again. Capture
    adds /event? cmd and removes a large atomic code block.
2016-05-31 Capture: add check byte to look for when corruption happones
2016-06-01 Capture: have ISR use register explicitly to reduce dynamic memory fragmentation
2016-06-03 Capture: add more byte checking, and report isr flags as status (status is broken)
2016-06-03 Capture: fix reporting of TOV1 and ICF1 in status
2016-06-04 Capture: remove t1vc from the capture isr
2016-06-04 Capture: move count into capture, and
    add mode and prescale to intiIcp1
2016-06-04 Capture: add the InitICP function
    to make the new command work
2016-06-05 Capture: prevent high/low capture
    unless mode is to track both edges
2016-06-09 Uart: fix some notes befor copy to Irrigate7
2016-06-15 Capture: buffer so icp3 can be added, and extern the double buffer
2016-06-16 Ht: for data loging an HT with the onboard adc connections to solar power.
2016-06-19 Adc: clear reference and mux more consistently before starting conversion
2016-06-23 Reflow: setup on my 30$ Walmart toaster oven
2016-06-23 Reflow: fix image link
2016-06-23 Reflow: do not modify the oven
2016-07-10 i2c-debug: makefile setup clean out ino files
    also reduce fuse setting duplication, and fix IO function names
2016-07-26 move ProcessCmd() into main, also adc has 1024 slots not 1023
2016-07-26 Adc: needs to have from 1 to 5 channel arguments
2016-07-28 Adc: lib not used
2016-08-02 Adc: add free running mode to auto_conversion
2016-08-06 CCtest: ported form Irrigate7
    updates in pins_board.h need ported back
2016-08-09 readme and notes
2016-08-27 BlinkLED: toggle has expected behavior now
2016-09-28 Uart: take addr for command from rpu bus manager
2016-09-29 i2c-debug: read rpu address from manager if available
2016-11-15 add hardware files
2016-11-15 Hardware: add test
2016-11-19 BlinkLED: no blocking
2016-11-19 Uart: blink fast if rpu mgr not found on i2c
2016-11-19 i2c-debug: blink fast if rpu mgr not found on i2c, and use the rpu_addr
    ouch found it... I was not passing the rpu_addr to
    StartEchoWhenAddressed()
2016-11-20 Adc: ch7 can now read PWR (e.g. battery)
    up to 15V (was 7.5V for 6V SLA)
2016-11-22 Digital: Wiring like digital control bridge
2016-11-22 Digital: readme
2016-11-29 Solenoid: init
    testing controls for K3 board
2016-11-29 Solenoid: cycle once at startup
2016-11-30 Solenoid: delay, runtime, and run are working
2016-11-30 Solenoid: add cmd pre (delay_start) and flow (flow_stop)
2016-12-01 Eeprom: add rpu_bus addr from I2C
2016-12-01 Hardware: evaluation and testing and reorg
    form epccs.org pages
2016-12-02 Solenoid: include Eeprom commands
2016-12-05 Eeprom: add uint16 and uint32 for use with solenoid
2016-12-05 Eeprom: macros don't work
2016-12-06 Solenoid: eeprom has a memory map loaded after initialization
2016-12-06 Solenoid: add cmd's /time, /flow, /stop
    , and flow_stop is /fstop cmd.
2016-12-07 Solenoid: add cmd's /save and /load.
    remove /ee? and /ee cmd.
2016-12-11 Solenoid: connected latching valves for evaluation
2016-12-11 Hardware: add schooling as markdown from other repo
2016-12-12 DayNight: a day/night state machine that uses the PV input voltage
2016-12-12 Hardware: markdown learning curve
2016-12-13 Solenoid: add day-night state machine to load from eeprom at start of day
2016-12-14 Solenoid: add cmd /analog?
2016-12-15 Capture: read rpu_bus adddress from twi
2016-12-15 Solenoid: init icp1 and add capture cmds /count?, /capture?, /event?
2016-12-16 Solenoid: eval of flow meter and K3 working togather
2016-12-16 Solenoid: evaluation of flow meter
2016-12-16 notes for ^6 and toolchain
2017-01-05 Hardware: evaluaiton day night state machine
2017-01-06 PwrMgt: power control of vin for shield
2017-01-07 PwrMgt: stop the blinking LED's during stable check, and more
2017-01-08 Hardware: power management notes e.g. vin to shield and ft/pulse sensor
2017-01-18 Hardware: ^6 review
2017-01-21 baud rate 38400 has .2% error 115200 has 2.1% error
2017-01-21 Schooling: baud rate notes for referance
2017-01-24 Hardware: bom and baud rate notes
2017-01-24 Hardware: evaluation pwr mgt with RPUpi ^1 shield
2017-02-09 Hardware: evaluation starts with K3^1 after some time with K3^0.
2017-02-16 Hardware: ^6 assyembly
2017-02-18 SelfTest: not done yet but a good save point
2017-02-19 Hardware: ^6 testing done, moving to evaluation
    note self-test
2017-03-23 Hardware: rm the 10k b=3380 thermistor
2017-03-25 Hardware: link to tindie store
2017-04-04 one line apt-get packages
2017-04-15 Hardware: use name icp rather than ft
2017-04-19 update tindie store link
2017-04-21 Hardware: circuit node names for bat-discon and vin-discon
2017-04-23 Hardware: flow sensor info on schematic
2017-04-25 Hardware: note on schematic about battery disconnect
2017-05-12 AmpHr: framework to measure solar power
2017-05-13 AmpHr: use day-nigh state machine and add a charge command
2017-05-14 AmpHr: one command shows charge and discharge accumulation
    from start of day
2017-05-14 AmpHr: report mAHr, attach callback
2017-05-18 BlinkLED: 'a' on UART stops blinking, send it from pyserial
2017-05-21 Bootloader: setup to build from source
2017-05-21 Bootloader: 250k bit/sec did not seem to work but this 115.2k does
2017-05-21 Bootloader: I should not assume IO13 is safe to blink
2017-05-21 Bootloader: CPPFLAGS is implicit, use it for common options
2017-05-23 Hardware: crystal capacitors, eagle is not for open hardware
2017-05-27 PwrMgt: add i to i2c cmd's and use with RPUpi test
2017-05-29 PwrMgt: add AmpHr and DayNight
2017-06-07 PwrMgt: add digital commands
2017-06-08 Solenoid: doc eeprom usage better
2017-06-10 Adc: add a way to calibrate from an eeprom value
2017-06-10 Adc: clean up regressions e.g. everything that uses analog
2017-06-12 SelfTest: save avcc referance into eeprom
2017-06-16 Parsing: use the rpu_addr from i2c
2017-06-16 Adc: size
2017-06-21 DayNight: add night work callback to start night lights
2017-06-22 Capture: ready to port to Irrigate7
2017-07-13 NightLight: work in progress
2017-07-15 Solenoid: perhaps a defined name for the solenoid state helps
2017-07-18 NightLight: somewhat working, need to remove capture and add AmpHr
2017-07-19 NightLight: icp removed, stop on mAHr accumulated discharge added
2017-07-19 AmpHr: load adc calibration from eeprom
2017-07-19 NightLight: command names not same as Solenoid
2017-07-19 NightLight: zero cycles at mAHr stop
2017-07-19 NightLight: add i2c commands
2017-08-13 DayNight: skip work callback if nothing got registered
2017-08-15 detect bootload port on Pi Zero or RPUftdi on Ubuntu
2017-08-15 Makefile BOOTLOAD_PORT
2017-08-23 SpiSlv: evaluation done, it works at 500kHz
2017-09-02 NightLight: evaluation
    100 Ohm added to status led
2017-09-26 Hardware: ^7 review, removed LT3652
2017-09-26 Hardware: ^7 reviewing
2017-10-14 Hardware: eval flow meter
2017-10-21 Hardware: ^7 testing
2017-10-24 Uart: report id without lt3652
2017-10-27 Reflow: setup for ^7 to use reflow oven
2017-10-28 Reflow: profile uploader needs rpu_addr
    and JSON changed for eeprom commands
2017-11-05 Hardware: ^8 update
2017-11-08 Hardware: ^8 boms
2017-11-18 Hardware: ^8 review
2017-12-13 Bootloader: updates for avr-gcc 5.4.0+Atmel3.6.0 and avrdude 6.3
2017-12-15 ^8 Testing done, 1v1 band-gap found in self-test which puts in eeprom
2017-12-23 Hardware: ^9 rethink this
2018-01-10 Hardware: ^9 keep the good ideas, but keep it general purpose also
2018-01-25 Hardware: ^9 rdy for review
2018-02-08 Hardware: PWR_I sense, SHLD_VIN gate stress
2018-04-19 Hardware: ^9 assembly
2018-04-24 SelfTest: update for ^9
2018-04-25 Digital: ^9 updates
2018-04-26 SpiSlv: changes for ^9
2018-04-27 CCtest: remove
2018-04-30 CurrSour: cli for current source control
2018-05-01 AmpHr: ^9 overhaul
2018-05-08 PwrMgt: ^9 update
2018-05-08 Ht: remove
2018-05-09 NightLight: ^9 updates
2018-05-14 DayNight: use NightLight wiring
2018-05-15 NightLight: ^9 updates checked
2018-05-17 Reflow: ^9 updates and add a light sensor to start profile
2018-05-17 Solenoid: ^9 updates (needs testing)
2018-05-17 Solenoid: wiring show flow sensor
2018-05-22 Hardware: tested two boards to list on tindie
2018-05-22 overview
2018-05-27 Alternat: charge a battery with solar power
2018-05-28 Alternat: count the number of times battery is at limit
2018-05-28 Alternat: doc
2018-06-03 NightLight: add alternate power input for solar panel
    bug noted in readme
2018-06-03 Solenoid: add alternat solar power, i2c, charge for battery use
2018-06-05 Hardware: ^9 evaluation with NightLight setup
2018-06-07 Hardware: ^9 evaluation with Solenoid setup
    github or TortoiseHg have changed so I expect to see a lot of LF to CRLF in updates
2018-06-08 lib: move some common argument test to parse
2018-06-09 KNL: combine NightLight with Solenoid and squeeze.
2018-06-10 Hardware: ^9 evaluation with KNL
2018-06-13 KNL: daynight threashold, rm kstop from night event
2018-06-22 use objdump to list source code with disassembly
2018-07-01 SpiSlv: use CE0 to drive nSS, weak pullup does 500k b/s
2018-07-13 https
2018-08-22 Hardware: three boards tested with salvaged parts for projects
2018-09-03 Hardware: BOM's for din-header-plug on ^9 got a look
2018-11-14 update doc in pin_num.h for ^9
2018-11-29 Adc: allow ch zero to give reading
2018-11-30 Capture: toggle icp current source to test, remove pwm
2018-12-10 DayNight: add sensor wiring
2018-12-12 notes
2018-12-15 i2c-debug: notes
2018-12-21 Solenoid: voltage divider on SLP003 solar pannel for light sensor
2019-01-03 try Travis CI with xenial
2019-01-20 Hardware: evaluation running three valves with K3 board
2019-02-24 Bootloader: use 38.4k bps since 111.1k is too far from 115.2k to be reliable
2019-02-26 Bootloader: save eeprom befor isp erase, add recover eeprom rule
2019-03-15 librarys need correct license
2019-03-15 also used as library
2019-03-19 SpiSlv: remove ADC2 notes
2019-03-22 libraries pin related need correct license
2019-03-25 uart peek removed
2019-03-26 documentation
2019-05-17 Bootloader: toolchain notes
2019-05-18 don't build a hex as part of the upload rule
2019-06-03 Hardware: notes from forum added to schooling
2019-06-03 uart glitch at init, optiboot does not glitch so do what it does.
2019-06-23 XcvrTest: wip, putting ideas in place
2019-07-01 XcvrTest: wip, smbus test added
2019-07-04 XcvrTest: test loopback of miso to mosi
2019-07-05 XcvrTest: add shutdown loopback to SCK
2019-07-07 XcvrTest: switch on/off test mode
2019-07-08 XcvrTest: cts to rts loopback test done with i2c testmode setting
2019-07-09 XcvrTest: tx and rx loopback test done with i2c testmode setting
2019-07-09 XcvrTest: dtr test done with i2c testmode setting
2019-07-09 XcvrTest: rx loopback
2019-07-11 XcvrTest: 100 ohm termination on both ends of rpubus.
2019-08-05 Bootloader: with linuxspi set fuse and load image with the one rule
2019-08-17 DayNight: locals are static, trais has bionic, vscode has remote

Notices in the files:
parts and their libraries:
J-BoardHDR: Copyright (C) 2013 Ronald Steven Sutherland
Released under the Creative Commons
Attribution Share-Alike 3.0 License
http://creativecommons.org/licenses/by-sa/3.0
H-Fiducial: under the terms of the GNU Free Documentation License, Version 1.2 or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
J-TP: Copyright (C) 2015 Ronald Sutherland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
